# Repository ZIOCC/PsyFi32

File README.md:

# Zuino XS PsyFi32 (ESP32, Qwiic, 3.3V, WIFI, BLE)

> This product can be available for purchase [here](https://www.smart-prototyping.com/Zuino-XS-PsyFi32.html).

#### Description

The PsyFi32 squeezes an ESP32 development platform into a board with the pinout of Sparkfun’s Pro Micro, and with a footprint that is only a teensy bit longer, is light as a feather and that we hope will be as commonly found on any workbench as oranges are in any grove.

Actually, one might say it looks suspiciously like an ESP32 Thing with slightly fewer pins (don’t worry, we picked them carefully) and without a battery charger. That’s because one of our employees came to us and said “I want an ESP32 Thing with a Pro Micro’s footprint, and with a Qwiic connector on it.” So here it is.

For your battery charging, monitoring, and regulating needs, we’ve created the ZIO LiPo Battery Manager, which can power the PsyFi32 and plenty of additional sensor and actuator modules over the Qwiic bus.

While you can certainly program this board with the Espressif native toolchain, we’ve made this board specifically for you Arduino fans out there, which is why we picked the form-factor of one of the most beloved and widely-used Arduino-compatible boards. 

And while you might not know it from the Sparkfun ESP32 Thing product page, the ESP32 Arduino Core is pretty full-featured at this point, including support for BLE and acting as a web server. (Let us know when you’ve updated your page, guys, so we can update ours. ;) )

To use with the Arduino IDE, install [Espressif's ESP32 Arduino core](https://github.com/espressif/arduino-esp32).

For our Mocap suit demo, we used Wire library files transplanted from [Stickbreaker's ESP32 Arduino Core fork](https://github.com/stickbreaker/arduino-esp32/tree/Wire-Destructor#development-status). 

In case you’re wondering about the name: it’s a trifecta of fun references.

> Note: As with all of the Version 1.0 Zio Qwiic boards, this board has been produced with the I2C pull-ups disconnected by default. If there's a significant length of wire between this board and your MCU, you'll need to solder closed the solder jumpers (labeled SDA, 3v3 and SCL) to connect the pull-up resistors to VCC.

##### PsyFi32 Dev Board PINMAP

#### Specification

* ESP32-D0WDQ6
* Weight 2.4g (0.084oz

#### Links

* [esp32_datasheet](https://www.smart-prototyping.com/image/data/NOA-RnD/101887%20Psyfi/esp32_datasheet_en.pdf)
* [Arduino core for the ESP32](https://github.com/espressif/arduino-esp32)
* [Eagle Files](https://github.com/ZIOCC/PsyFi32)
* [Very Detailed Introduction for ESP32 on Instructables.com](https://www.instructables.com/id/IOT-Made-Simple-Playing-With-the-ESP32-on-Arduino-/)

> ###### About Zio
> Zio is a new line of open sourced, compact, and grid layout boards, fully integrated for Arduino and Qwiic ecosystem. Designed ideally for wearables, robotics, small-space limitations or other on the go projects. Check out other awesome Zio products [here](https://www.smart-prototyping.com/Zio).

> All Zio products are released under the [Creative Commons Attribution, Share-Alike License](https://creativecommons.org/licenses/by-sa/4.0/), and in accordance with the principles of the [Open Source Hardware Association's OSHW Statement of Principles 1.0 and OSHW Definition 1.0](https://www.oshwa.org/definition/).

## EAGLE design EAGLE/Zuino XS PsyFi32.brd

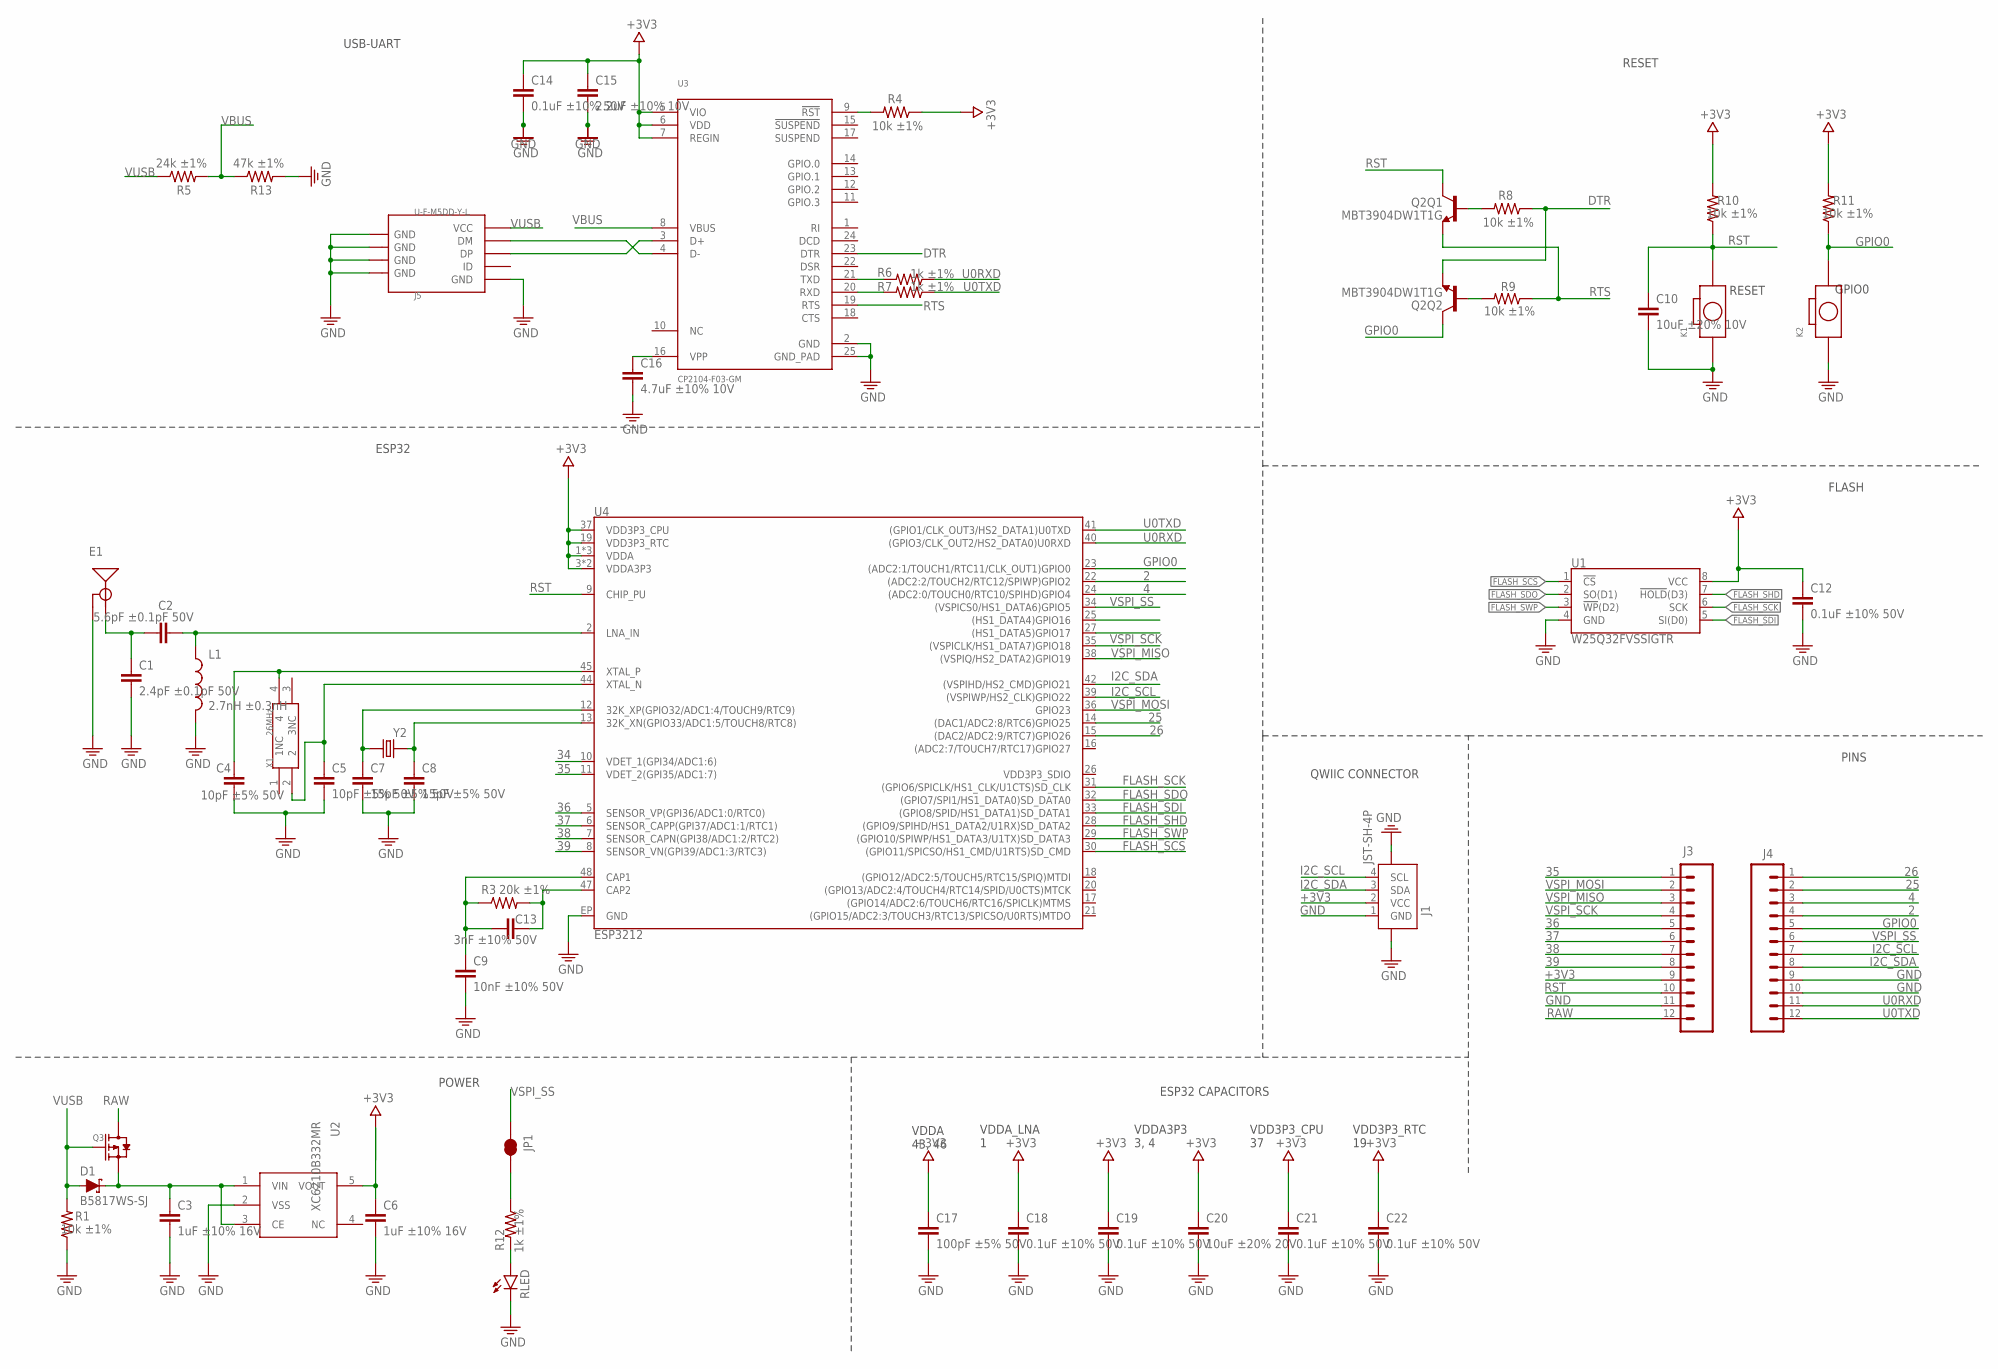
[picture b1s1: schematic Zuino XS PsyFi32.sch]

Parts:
C1: 2.4pF ±0.1pF 50V; YAGEO_C_0402
C2: 5.6pF ±0.1pF 50V; YAGEO_C_0402
C3, C6: 1uF ±10% 16V; YAGEO_C_0402
C4, C5: 10pF ±5% 50V; YAGEO_C_0402
C7, C8: 15pF ±5% 50V; YAGEO_C_0402
C9: 10nF ±10% 50V; YAGEO_C_0402
C10: 10uF ±20% 10V; YAGEO_C_0402
C12, C14, C18, C19, C21, C22: 0.1uF ±10% 50V; YAGEO_C_0402
C13: 3nF ±10% 50V; YAGEO_C_0402
C15: 2.2uF ±10% 10V; YAGEO_C_0402
C16: 4.7uF ±10% 10V; YAGEO_C_0402
C17: 100pF ±5% 50V; YAGEO_C_0402
C20: 10uF ±20% 20V; YAGEO_C_0402
D1: B5817WS-SJ; SOD-323
D2: RLED; LED_HSMH-C190
E1: ANTENNA-GROUNDED; ANTENNA_ESP32
J1: JST-SH-4P; JST-SH-4P-90
J3, J4: CONN_12; 1X12
J5: U-F-M5DD-Y-L; MICRO-SMD
JP1: JUMPER-SMT_2_NC_TRACE_SILK; SMT-JUMPER_2_NC_TRACE_SILK
K1, K2: BOTTON-2PSKRKAEE020; SKRKAEE020
L1: 2.7nH ±0.3nH; INDUCTOR_HK10052N7S-T
Q2: MBT3904DW1T1G; SC70-6
Q3: MOSFET-P-323; SOT-323
R1, R4, R8, R9, R10, R11: 10k ±1%; YAGEO_R_0402
R3: 20k ±1%; YAGEO_R_0402
R5: 24k ±1%; YAGEO_R_0402
R6, R7, R12: 1k ±1%; YAGEO_R_0402
R13: 47k ±1%; YAGEO_R_0402
U1: W25Q32FVSSIGTR; SOIC-8
U2: XC6210B332MR; SOT23-5
U3: CP2104-F03-GM; QFN24-CP2104
U4: ESP3212; QFN48-0.4MM
X1: 26MHz; 4P-SMD-2X1.6MM
Y2: 32.768kHz; CRYSTAL_2012

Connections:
2: J4.4, U4.22 ((ADC2:2/TOUCH2/RTC12/SPIWP)GPIO2)
4: J4.3, U4.24 ((ADC2:0/TOUCH0/RTC10/SPIHD)GPIO4)
25: J4.2, U4.14 ((DAC1/ADC2:8/RTC6)GPIO25)
26: J4.1, U4.15 ((DAC2/ADC2:9/RTC7)GPIO26)
34: U4.10 (VDET_1(GPI34/ADC1:6))
35: J3.1, U4.11 (VDET_2(GPI35/ADC1:7))
36: J3.5, U4.5 (SENSOR_VP(GPI36/ADC1:0/RTC0))
37: J3.6, U4.6 (SENSOR_CAPP(GPI37/ADC1:1/RTC1))
38: J3.7, U4.7 (SENSOR_CAPN(GPI38/ADC1:2/RTC2))
39: J3.8, U4.8 (SENSOR_VN(GPI39/ADC1:3/RTC3))
+3V3: C6.1, C12.1, C14.1, C15.1, C17.1, C18.1, C19.1, C20.1, C21.1, C22.1, J1.2 (VCC), J3.9, R4.1, R10.2, R11.2, U1.8 (VCC), U2.5 (VOUT), U3.5 (VIO), U3.6 (VDD), U3.7 (REGIN), U4.1 (VDDA), U4.3 (VDDA3P3), U4.4 (VDDA3P3), U4.19 (VDD3P3_RTC), U4.37 (VDD3P3_CPU), U4.43 (VDDA), U4.46 (VDDA)
DTR: Q2.1 (E), R8.1, U3.23 (DTR)
FLASH_SCK: U1.6 (SCK), U4.31 ((GPIO6/SPICLK/HS1_CLK/U1CTS)SD_CLK)
FLASH_SCS: U1.1 (!CS!), U4.30 ((GPIO11/SPICSO/HS1_CMD/U1RTS)SD_CMD)
FLASH_SDI: U1.5 (SI(D0)), U4.33 ((GPIO8/SPID/HS1_DATA1)SD_DATA1)
FLASH_SDO: U1.2 (SO(D1)), U4.32 ((GPIO7/SPI1/HS1_DATA0)SD_DATA0)
FLASH_SHD: U1.7 (!HOLD!(D3)), U4.28 ((GPIO9/SPIHD/HS1_DATA2/U1RX)SD_DATA2)
FLASH_SWP: U1.3 (!WP!(D2)), U4.29 ((GPIO10/SPIWP/HS1_DATA3/U1TX)SD_DATA3)
GND: C1.2, C3.2, C4.2, C5.2, C6.2, C7.2, C8.2, C9.2, C10.2, C12.2, C14.2, C15.2, C16.2, C17.2, C18.2, C19.2, C20.2, C21.2, C22.2, D2.1 (C), E1.GND, J1.1 (GND), J1.5, J1.6, J3.11, J4.9, J4.10, J5.GND, J5.S1 (GND), J5.S1@1 (GND), J5.S1@2 (GND), J5.S2 (GND), J5.S2@1 (GND), J5.S2@2 (GND), J5.S3 (GND), J5.S3@1 (GND), J5.S3@2 (GND), J5.S4 (GND), J5.S4@1 (GND), J5.S4@2 (GND), K1.1, K2.1, L1.2, R1.1, R13.2, U1.4 (GND), U2.2 (VSS), U3.2 (GND), U3.25 (GND_PAD), U4.EP (GND)
GPIO0: J4.5, K2.2, Q2.6 (C), R11.1, U4.23 ((ADC2:1/TOUCH1/RTC11/CLK_OUT1)GPIO0)
I2C_SCL: J1.4 (SCL), J4.7, U4.39 ((VSPIWP/HS2_CLK)GPIO22)
I2C_SDA: J1.3 (SDA), J4.8, U4.42 ((VSPIHD/HS2_CMD)GPIO21)
unnamed: C7.1, U4.12 (32K_XP(GPIO32/ADC1:4/TOUCH9/RTC9)), Y2.1
unnamed: C8.1, U4.13 (32K_XN(GPIO33/ADC1:5/TOUCH8/RTC8)), Y2.2
unnamed: C9.1, C13.1, R3.1, U4.48 (CAP1)
unnamed: C4.1, U4.45 (XTAL_P), X1.4
unnamed: C5.1, U4.44 (XTAL_N), X1.2
unnamed: C13.2, R3.2, U4.47 (CAP2)
unnamed: C1.1, C2.1, E1.ANT (SIGNAL)
unnamed: C2.2, L1.1, U4.2 (LNA_IN)
unnamed: R6.2, U3.21 (TXD)
unnamed: J5.D+ (DP), U3.3 (D+)
unnamed: J5.D- (DM), U3.4 (D-)
unnamed: R4.2, U3.9 (!RST)
unnamed: R7.2, U3.20 (RXD)
unnamed: Q2.2 (B), R9.2
unnamed: Q2.5 (B), R8.2
unnamed: D2.2 (A), R12.2
unnamed: C16.1, U3.16 (VPP)
unnamed: JP1.2, R12.1
RAW: J3.12, Q3.3 (D)
RST: C10.1, J3.10, K1.2, Q2.3 (C), R10.1, U4.9 (CHIP_PU)
RTS: Q2.4 (E), R9.1, U3.19 (RTS)
U0RXD: J4.11, R6.1, U4.40 ((GPIO3/CLK_OUT2/HS2_DATA0)U0RXD)
U0TXD: J4.12, R7.1, U4.41 ((GPIO1/CLK_OUT3/HS2_DATA1)U0TXD)
VBUS: R5.2, R13.1, U3.8 (VBUS)
VIN: C3.1, D1.C, Q3.2 (S), U2.1 (VIN), U2.3 (CE)
VSPI_MISO: J3.3, U4.38 ((VSPIQ/HS2_DATA2)GPIO19)
VSPI_MOSI: J3.2, U4.36 (GPIO23)
VSPI_SCK: J3.4, U4.35 ((VSPICLK/HS1_DATA7)GPIO18)
VSPI_SS: J4.6, JP1.1, U4.34 ((VSPICS0/HS1_DATA6)GPIO5)
VUSB: D1.A, J5.VBUS (VCC), Q3.1 (G), R1.2, R5.1

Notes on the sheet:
RESET
GPIO0
VDDA 43, 46
VDDA_LNA 1
VDDA3P3 3, 4
VDD3P3_CPU 37
VDD3P3_RTC 19
ESP32
FLASH
PINS
USB-UART
POWER
ESP32 CAPACITORS
QWIIC CONNECTOR

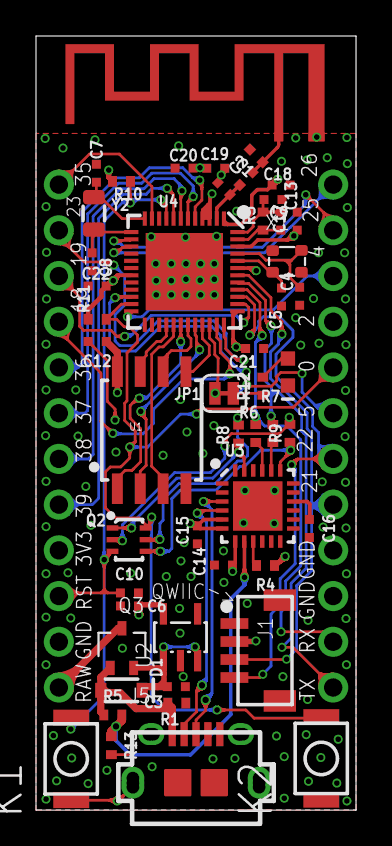
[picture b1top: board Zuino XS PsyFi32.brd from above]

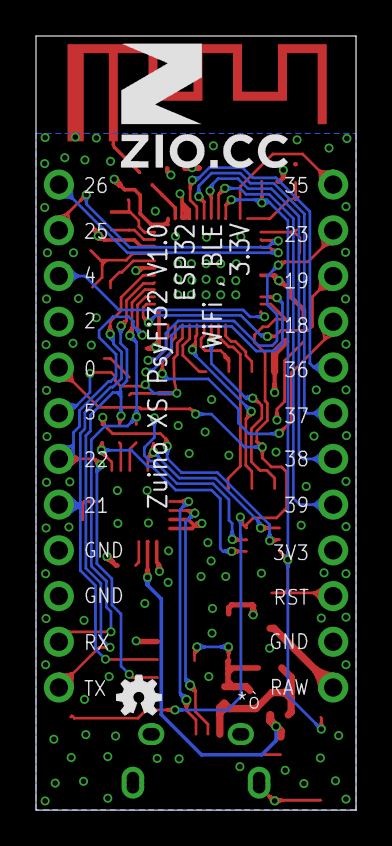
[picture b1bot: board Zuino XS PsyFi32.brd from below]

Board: 4 copper layers, 17.8 x 43.0 mm, 54 parts (2 on the bottom side), 51 nets.

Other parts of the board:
U$1: SPARKFUN-AESTHETICS_OSHW-LOGO-MINI
U$18: 7MM

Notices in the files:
parts and their libraries:
SparkFun-DiscreteSemi: Licensing: Creative Commons ShareAlike 4.0 International - https://creativecommons.org/licenses/by-sa/4.0
SparkFun-DigitalIC: Licensing: CC v3.0 Share-Alike You are welcome to use this library for commercial purposes.
